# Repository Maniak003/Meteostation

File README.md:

<!DOCTYPE html>
<html lang="en" data-color-mode="auto" data-light-theme="light" data-dark-theme="dark">
  <head>
    <meta charset="utf-8">
  </head>
    <body class="logged-in env-production page-responsive page-blob" style="word-wrap: break-word;">
      <p> Meteostation with radiation monitor. </p>

    </body>
</html>

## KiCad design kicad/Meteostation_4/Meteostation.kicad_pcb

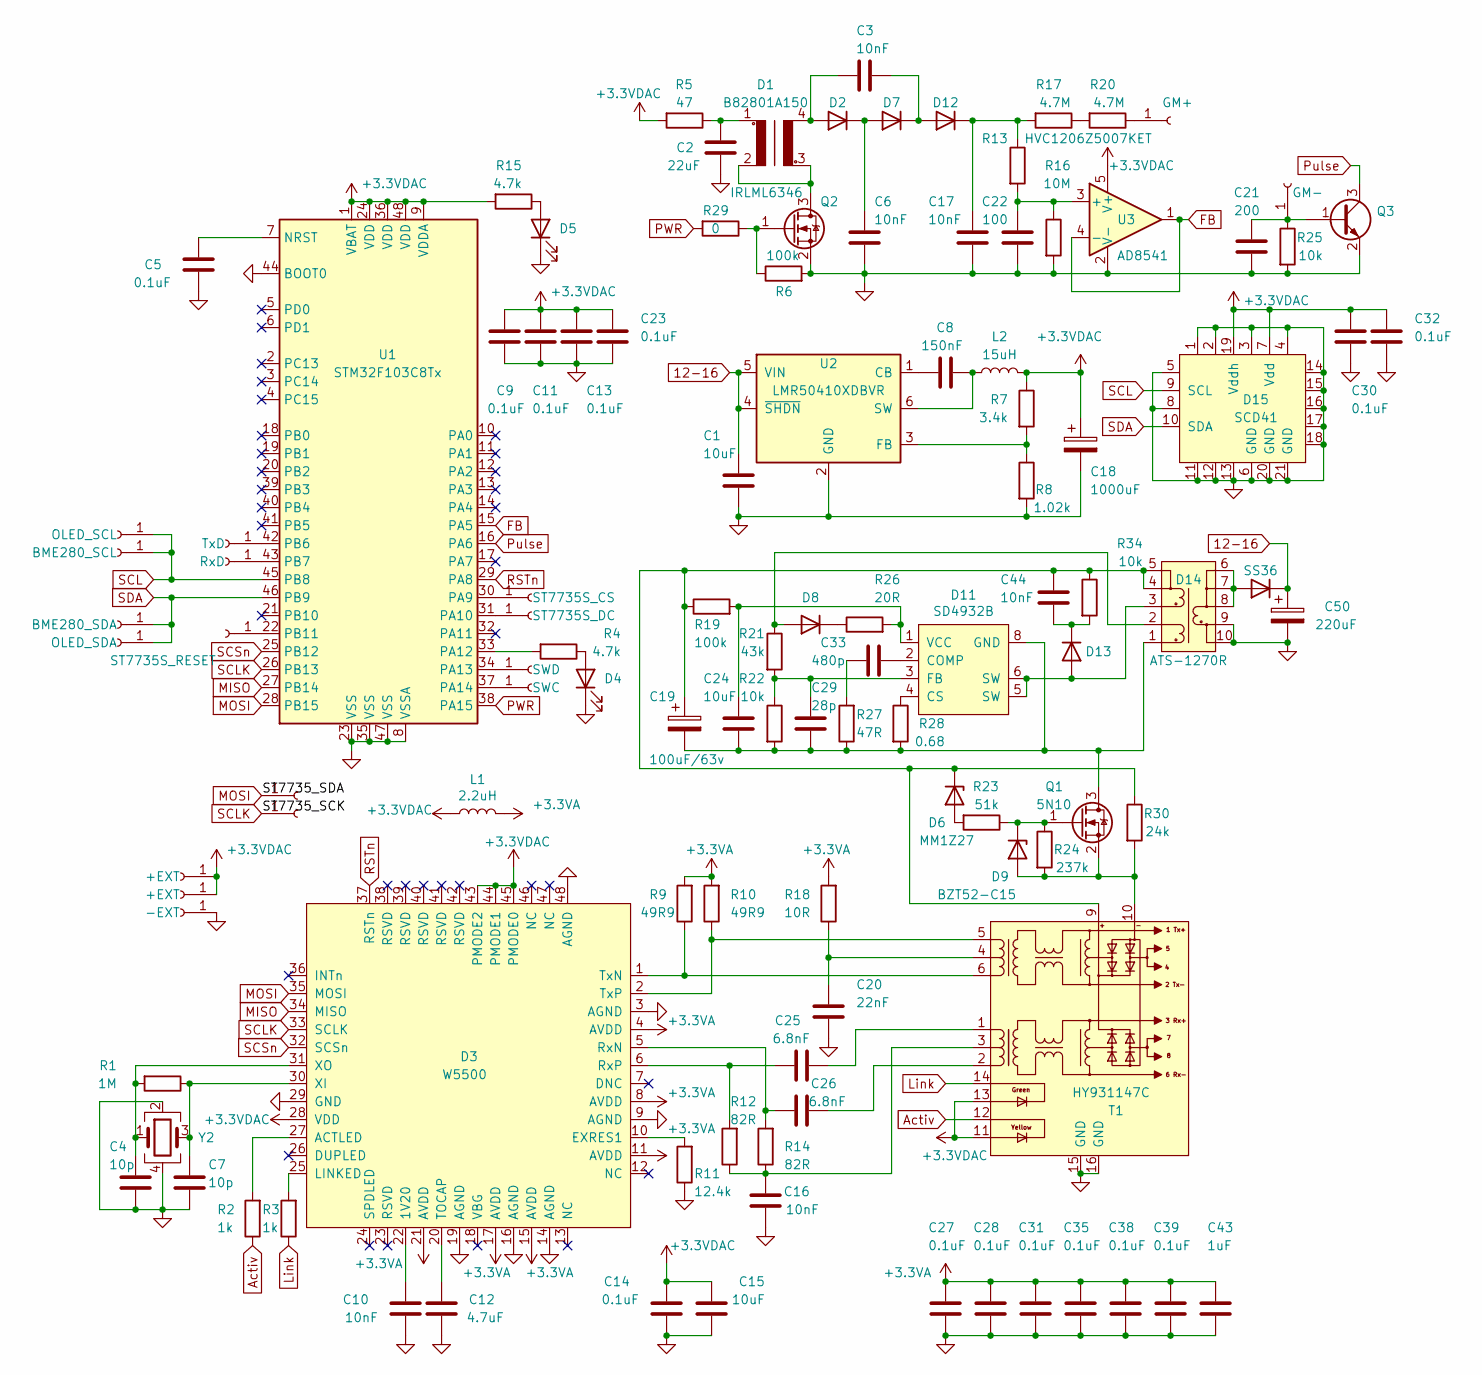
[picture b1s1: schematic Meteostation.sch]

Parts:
C1, C24: 10uF; C_0805_2012Metric
C2: 22uF; C_0805_2012Metric
C3, C6, C17: 10nF; C_1206_3216Metric
C4, C7: 10p; C_0402_1005Metric
C5, C14, C27, C28, C31, C35, C38, C39: 0.1uF; C_0402_1005Metric
C8: 150nF; C_0603_1608Metric
C9, C11, C13, C30, C32: 0.1uF; C_0603_1608Metric
C10: 10nF; C_0402_1005Metric
C12: 4.7uF; C_0402_1005Metric
C15: 10uF; C_0603_1608Metric
C16, C44: 10nF; C_0603_1608Metric
C18: 1000uF; CP_EIA-7343-15_Kemet-W
C19: 100uF/63v; CAP_horizontal
C20: 22nF; C_0603_1608Metric
C21: 200; C_0402_1005Metric
C22: 100; C_0402_1005Metric
C23: 0.1uF; C_0805_2012Metric
C25, C26: 6.8nF; C_0402_1005Metric
C29: 28p; C_0603_1608Metric
C33: 480p; C_0603_1608Metric
C43: 1uF; C_0402_1005Metric
C50: 220uF; CP_EIA-7343-15_Kemet-W
D1: B82801A150; B82801A1
D2, D7, D12: D; D_SOD-123
D3: W5500; LQFP-48_7x7mm_P0.5mm
D4, D5: LED; LED_0603_1608Metric
D6: MM1Z27; D_SOD-123
D8, D13: FR107W F7; D_SOD-123F
D9: BZT52-C15; D_SOD-123
D11: SD4932B; SOIC-8-N7_3.9x4.9mm_P1.27mm
D14: ATS-1270R; DA2257
D15: SCD41
D16: SS36; D_SMA
J1: TxD; ConnMini
J2: RxD; ConnMini
J3: BME280_SCL; SMD-CONN
J4: BME280_SDA; SMD-CONN
J5: +EXT; ConnMini
J6: +EXT; SMD-CONN
J7: -EXT; SMD-CONN
J8: mosi; ConnMini
J9: sclk; ConnMini
J10: GM+; SMD-CONN
J11: GM-; SMD-CONN
J12: SWD; ConnMini
J13: SWC; ConnMini
J14: ST7735S_CS; mini_conn
J15: OLED_SCL; SMD-CONN
J16: OLED_SDA; SMD-CONN
J17: ST7735S_DC; mini_conn
J18: ST7735S_RESET; mini_conn
L1: 2.2uH; L_0805_2012Metric
L2: 15uH; L_Abracon_ASPI-0630LR
Q1: 5N10; SOT-23
Q2: IRLML6346; SOT-23
Q3: Q_NPN_BEC; SOT-23
R1: 1M; R_0402_1005Metric
R2, R3: 1k; R_0402_1005Metric
R4: 4.7k; R_0402_1005Metric
R5: 47; R_1206_3216Metric
R6, R19: 100k; R_0603_1608Metric
R7: 3.4k; R_0603_1608Metric
R8: 1.02k; R_0603_1608Metric
R9, R10: 49R9; R_0603_1608Metric
R11: 12.4k; R_0402_1005Metric
R12, R14: 82R; R_0402_1005Metric
R13: HVC1206Z5007KET; R_1206_3216Metric
R15: 4.7k; R_0603_1608Metric
R16: 10M; R_0402_1005Metric
R17, R20: 4.7M; R_0603_1608Metric
R18: 10R; R_0603_1608Metric
R21: 43k; R_0603_1608Metric
R22, R34: 10k; R_0603_1608Metric
R23: 51k; R_0603_1608Metric
R24: 237k; R_0603_1608Metric
R25: 10k; R_0402_1005Metric
R26: 20R; R_0603_1608Metric
R27: 47R; R_0603_1608Metric
R28: 0.68; R_0603_1608Metric
R29: 0; R_1206_3216Metric
R30: 24k; R_0603_1608Metric
T1: HY931147C
U1: STM32F103C8Tx; LQFP-48_7x7mm_P0.5mm
U2: LMR50410XDBVR; SOT-23-6
U3: AD8541; TSOT-23-5
Y2: ECS-250-20-33 25MHz; Crystal_SMD_SeikoEpson_FA238-4Pin_3.2x2.5mm

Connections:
12-16: C1.1, C50.1, D16.1 (K), U2.4 (~SHDN), U2.5 (VIN)
+3.3VA: C27.1, C28.1, C31.1, C35.1, C38.1, C39.1, C43.1, D3.4 (AVDD), D3.8 (AVDD), D3.11 (AVDD), D3.15 (AVDD), D3.17 (AVDD), D3.21 (AVDD), L1.2, R9.2, R10.2, R18.2
+3.3VDAC: C9.1, C11.1, C13.1, C14.2, C15.2, C18.1, C23.1, C30.1, C32.1, D3.28 (VDD), D3.43 (PMODE2), D3.44 (PMODE1), D3.45 (PMODE0), D15.7 (Vdd), D15.19 (Vddh), J5.1, J6.1, L1.1, L2.2, R5.2, R7.1, R15.2, T1.11, T1.13, U1.1 (VBAT), U1.9 (VDDA), U1.24 (VDD), U1.36 (VDD), U1.48 (VDD), U3.5 (V+)
Activ: R2.1, T1.12
FB: U1.15 (PA5), U3.1, U3.4 (-)
GND: C1.2, C2.2, C4.2, C5.1, C6.2, C7.2, C9.2, C10.1, C11.2, C12.1, C13.2, C14.1, C15.1, C16.1, C17.2, C18.2, C20.2, C21.1, C22.1, C23.2, C27.2, C28.2, C30.2, C31.2, C32.2, C35.2, C38.2, C39.2, C43.2, C50.2, D3.3 (AGND), D3.9 (AGND), D3.14 (AGND), D3.16 (AGND), D3.19 (AGND), D3.29 (GND), D3.48 (AGND), D4.1 (K), D5.1 (K), D14.9, D14.10, D15.1, D15.2, D15.3, D15.4, D15.5, D15.6 (GND), D15.8, D15.11, D15.12, D15.13, D15.14, D15.15, D15.16, D15.17, D15.18, D15.20 (GND), D15.21 (GND), J7.1, Q2.2 (S), Q3.2 (E), R6.2, R8.2, R11.1, R16.2, R25.2, T1.15 (GND), T1.16 (GND), U1.8 (VSSA), U1.23 (VSS), U1.35 (VSS), U1.44 (BOOT0), U1.47 (VSS), U2.2 (GND), U3.2 (V-), Y2.2, Y2.4
Link: R3.1, T1.14
MISO: D3.34 (MISO), U1.27 (PB14)
MOSI: D3.35 (MOSI), J8.1, U1.28 (PB15)
unnamed: C2.1, D1.1, R5.1
unnamed: C16.2, R12.1, R14.1, T1.3
unnamed: C20.1, R18.1, T1.4
unnamed: C25.2, T1.1
unnamed: C26.2, T1.2
unnamed: C33.2, R27.2
unnamed: C3.2, D1.4, D2.2 (A)
unnamed: C6.1, D2.1 (K), D7.2 (A)
unnamed: C10.2, D3.22 (1V20)
unnamed: D3.27 (ACTLED), R2.2
unnamed: D3.10 (EXRES1), R11.2
unnamed: D3.25 (LINKED), R3.2
unnamed: C26.1, D3.5 (RxN), R14.2
unnamed: C25.1, D3.6 (RxP), R12.2
unnamed: C12.2, D3.20 (TOCAP)
unnamed: D3.1 (TxN), R9.1, T1.6
unnamed: D3.2 (TxP), R10.1, T1.5
unnamed: C7.1, D3.30 (XI), R1.1, Y2.3
unnamed: C4.1, D3.31 (XO), R1.2, Y2.1
unnamed: D4.2 (A), R4.1
unnamed: D5.2 (A), R15.1
unnamed: D6.2 (A), R23.2
unnamed: C19.1, C44.1, D6.1 (K), D14.4, D14.5, R19.1, R30.1, R34.1, T1.9
unnamed: D8.2 (A), D14.2, R21.1
unnamed: D8.1 (K), R26.1
unnamed: D9.2 (A), Q1.2 (S), R24.2, R30.2, T1.10
unnamed: D9.1 (K), Q1.1 (G), R23.1, R24.1
unnamed: C33.1, D11.2 (COMP)
unnamed: D11.4 (CS), R28.1
unnamed: C29.1, D11.3 (FB), R21.2, R22.1
unnamed: C19.2, C24.2, C29.2, D11.8 (GND), D14.1, Q1.3 (D), R22.2, R27.1, R28.2
unnamed: C24.1, D11.1 (VCC), R19.2, R26.2
unnamed: C3.1, D7.1 (K), D12.2 (A)
unnamed: C17.1, D12.1 (K), R13.1, R17.2
unnamed: D11.5 (SW), D11.6 (SW), D13.2 (A), D14.3
unnamed: C44.2, D13.1 (K), R34.2
unnamed: D14.6, D14.7, D14.8, D16.2 (A)
unnamed: J1.1, U1.42 (PB6)
unnamed: J2.1, U1.43 (PB7)
unnamed: J10.1, R20.1
unnamed: C21.2, J11.1, Q3.1 (B), R25.1
unnamed: J12.1, U1.34 (PA13)
unnamed: J13.1, U1.37 (PA14)
unnamed: J14.1, U1.30 (PA9)
unnamed: J17.1, U1.31 (PA10)
unnamed: J18.1, U1.22 (PB11)
unnamed: D1.2, D1.3, Q2.3 (D)
unnamed: Q2.1 (G), R6.1, R29.1
unnamed: R17.1, R20.2
unnamed: C5.2, U1.7 (NRST)
unnamed: R4.2, U1.33 (PA12)
unnamed: C8.1, U2.1 (CB)
unnamed: R7.2, R8.1, U2.3 (FB)
unnamed: C8.2, L2.1, U2.6 (SW)
unnamed: C22.2, R13.2, R16.1, U3.3 (+)
PWR: R29.2, U1.38 (PA15)
Pulse: Q3.3 (C), U1.16 (PA6)
RSTn: D3.37 (RSTn), U1.29 (PA8)
SCL: D15.9 (SCL), J3.1, J15.1, U1.45 (PB8)
SCLK: D3.33 (SCLK), J9.1, U1.26 (PB13)
SCSn: D3.32 (SCSn), U1.25 (PB12)
SDA: D15.10 (SDA), J4.1, J16.1, U1.46 (PB9)

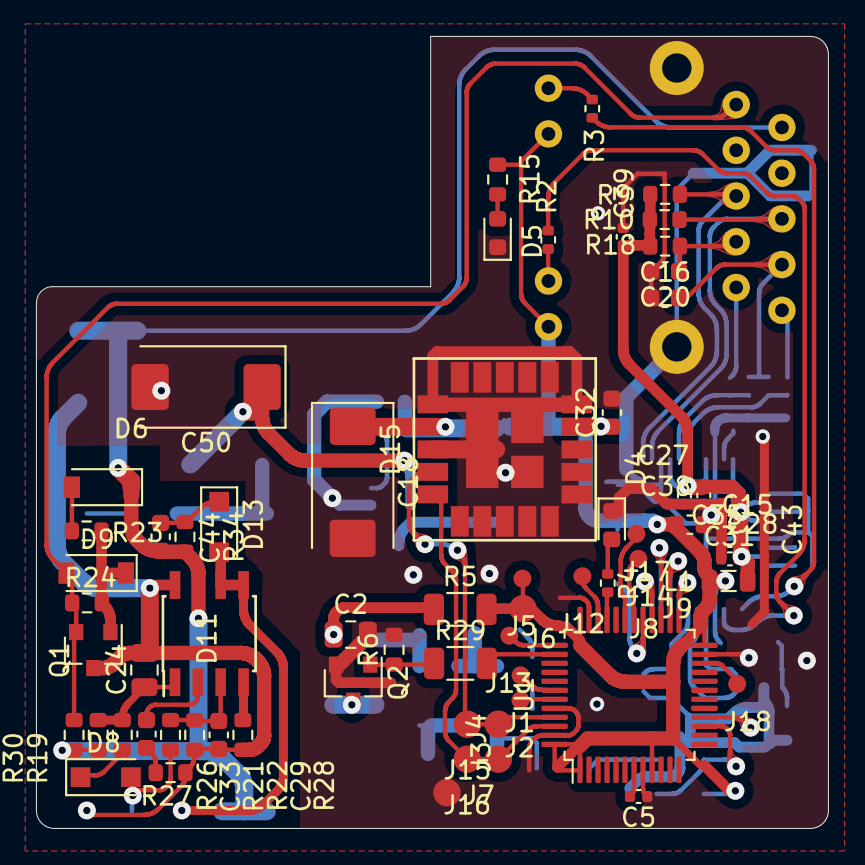
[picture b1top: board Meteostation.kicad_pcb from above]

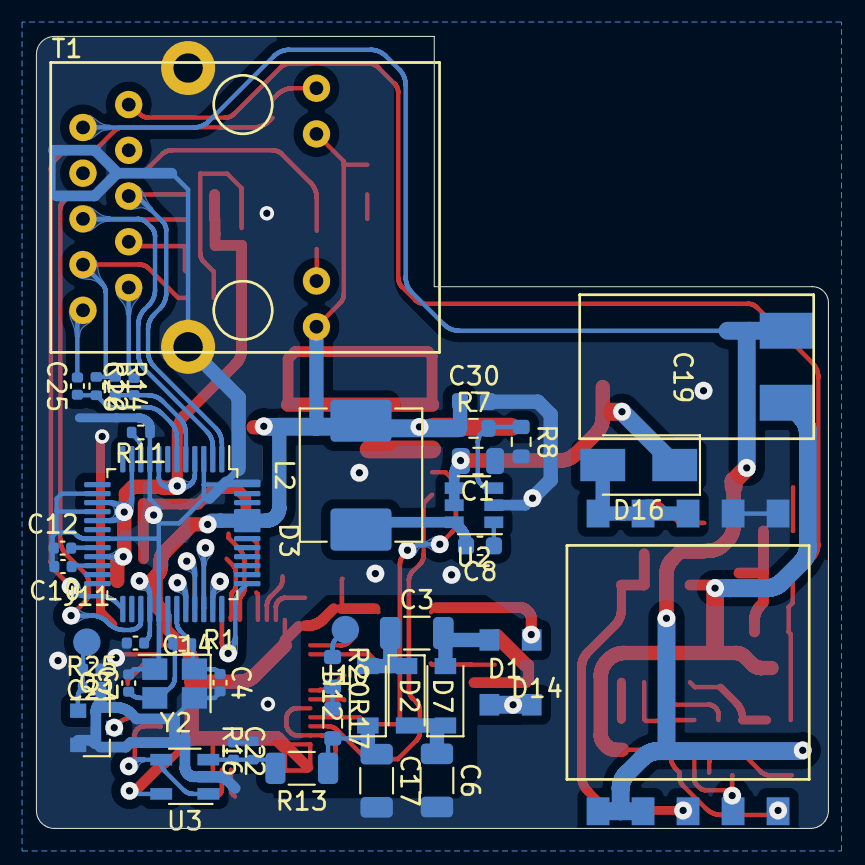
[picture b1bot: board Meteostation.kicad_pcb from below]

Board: 2 copper layers, 44.0 x 44.0 mm, 109 parts (42 on the bottom side), 71 nets.

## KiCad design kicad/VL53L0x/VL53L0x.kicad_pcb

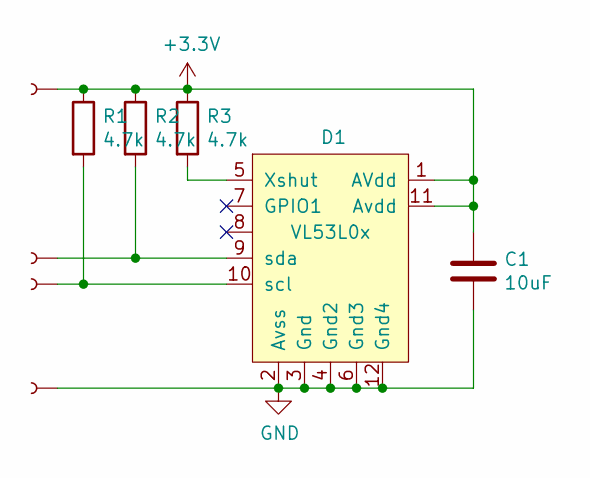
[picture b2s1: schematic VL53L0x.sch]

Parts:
C1: 10uF; C_0402_1005Metric
D1: VL53L0x
J1, J2, J3, J4: Conn; ConnMini
R1, R2, R3: 4.7k; R_0402_1005Metric

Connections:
+3V3: C1.1, D1.1 (AVdd), D1.11 (Avdd), J1.1, R1.1, R2.1, R3.1
GND: C1.2, D1.2 (Avss), D1.3 (Gnd), D1.4 (Gnd2), D1.6 (Gnd3), D1.12 (Gnd4), J4.1
unnamed: D1.5 (Xshut), R3.2
unnamed: D1.9 (sda), J2.1, R2.2
unnamed: D1.10 (scl), J3.1, R1.2

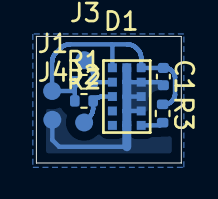
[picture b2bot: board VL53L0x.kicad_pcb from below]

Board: 2 copper layers, 8.1 x 7.0 mm, 9 parts (9 on the bottom side), 5 nets.

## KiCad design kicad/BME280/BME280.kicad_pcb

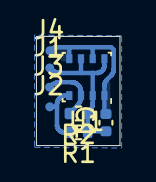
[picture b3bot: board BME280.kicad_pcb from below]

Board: 2 copper layers, 4.6 x 6.1 mm, 8 parts (8 on the bottom side), 4 nets.

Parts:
C1: 0.1uF; C_0402_1005Metric
J1, J2, J3, J4: Conn; ConnMini
R1, R2: 5.1k; R_0402_1005Metric
U1: BME280; Bosch_LGA-8_2.5x2.5mm_P0.65mm_ClockwisePinNumbering

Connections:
Gnd: C1.2, J4.1, U1.1, U1.5, U1.7
SCL: J2.1, R1.2, U1.4
SDA: J3.1, R2.2, U1.3
Vcc: C1.1, J1.1, R1.1, R2.1, U1.2, U1.6, U1.8

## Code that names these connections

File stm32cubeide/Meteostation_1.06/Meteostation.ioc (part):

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Mcu.UserName=STM32F103C8Tx
PA12.GPIOParameters=GPIO_Speed,PinState,GPIO_Label
PA9.GPIOParameters=GPIO_Label
PA6.GPIO_Label=PULSE_GM
PB11.Signal=GPIO_Output
PB15.Signal=SPI2_MOSI
PB13.Signal=SPI2_SCK
RCC.SYSCLKSource=RCC_SYSCLKSOURCE_PLLCLK
PA15.GPIO_Label=POWER_PULSE
PA12.Signal=GPIO_Output
PB6.Signal=USART1_TX
PB6.Mode=Asynchronous
PA8.GPIOParameters=GPIO_Label
PA12.PinState=GPIO_PIN_RESET
PB12.GPIO_Label=Eth_CS
PA6.GPIO_PuPd=GPIO_PULLUP
PB14.Mode=Full_Duplex_Master
PA10.GPIO_Label=ST7735S_DC
PB7.Signal=USART1_RX
PA8.Signal=GPIO_Output
PB9.Signal=I2C1_SDA
Mcu.Package=LQFP48
PA6.Signal=GPXTI6
PA10.Signal=GPIO_Output
PA15.Signal=GPIO_Output
PA5.GPIOParameters=GPIO_Label
PB13.Mode=Full_Duplex_Master
PA12.GPIO_Speed=GPIO_SPEED_FREQ_HIGH
PA6.GPIOParameters=GPIO_PuPd,GPIO_Label,GPIO_ModeDefaultEXTI
PA6.GPIO_ModeDefaultEXTI=GPIO_MODE_IT_RISING
PB8.GPIOParameters=GPIO_Label
PB9.GPIO_Label=BME280_SDA
PA15.GPIOParameters=GPIO_Speed,GPIO_Label
PA9.GPIO_Label=ST7735S_CS
PB11.GPIO_Label=ST7735S_RESET
PA12.GPIO_Label=LED
PB9.GPIOParameters=GPIO_Label
PB8.GPIO_Label=BME280_SCL
PA8.GPIO_Label=Eth_rst
PB9.Mode=I2C
PA9.Signal=GPIO_Output
PB11.GPIOParameters=GPIO_Label
PB12.GPIO_Speed=GPIO_SPEED_FREQ_HIGH
PB14.Signal=SPI2_MISO
PA5.Signal=ADCx_IN5
board=custom
PB15.Mode=Full_Duplex_Master
PA10.GPIOParameters=GPIO_Label
Mcu.Name=STM32F103C(8-B)Tx
RCC.SYSCLKFreq_VALUE=64000000
PA5.GPIO_Label=FB
RCC.HSEDivPLL=RCC_HSE_PREDIV_DIV2
PA15.GPIO_Speed=GPIO_SPEED_FREQ_HIGH
PB7.Mode=Asynchronous
PB8.Mode=I2C
PB8.Signal=I2C1_SCL
PB12.GPIOParameters=GPIO_Speed,GPIO_Label
PB12.Signal=GPIO_Output

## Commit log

2022-09-04 удалено: Documents/12_100229_1_85526.pdf удалено: Documents/2022_04_03_20_00_22_110.png удалено: Documents/Diagram.pdf удалено: Documents/IMG_20220105_221915.jpg удалено: Documents/IMG_20220105_22192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
2022-09-04 новый файл: Arduino/meteomonitor/meteomonitor.ino новый файл: FreeCAD/box.FCStd новый файл: FreeCAD/box.stl
2022-09-05 изменено: kicad/Meteostation_3/Meteostation.kicad_pcb изменено: kicad/Meteostation_3/Meteostation.kicad_pcb-bak изменено: kicad/Meteostation_3/Meteostation.sch изменено: kicad/Meteostation_3/Meteosta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
2022-09-05 изменено: FreeCAD/box.FCStd изменено: FreeCAD/box.stl
2022-09-08 изменено: FreeCAD/box.FCStd изменено: FreeCAD/box.stl новый файл: kicad/Meteostation_4/Meteostation-cache.lib новый файл: kicad/Meteostation_4/Meteostation-rescue.bck новый файл: kicad/Meteostation_4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
2022-09-08 новый файл: Documents/Sensirion_CO2_Sensors_SCD4x_Datasheet.pdf
2022-09-09 новый файл: Documents/5N10.pdf изменено: kicad/Meteostation_4/Meteostation.kicad_pcb изменено: kicad/Meteostation_4/Meteostation.kicad_pcb-bak изменено: kicad/Meteostation_4/Meteostation.sch изменено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
2022-09-11 изменено: kicad/Meteostation_4/Meteostation-cache.lib изменено: kicad/Meteostation_4/Meteostation-rescue.lib изменено: kicad/Meteostation_4/Meteostation.kicad_pcb изменено: kicad/Meteostation_4/Meteo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
2022-09-13 изменено: kicad/Meteostation_4/gerber/Meteostation.zip новый файл: stm32cubeide/Meteostation/.cproject новый файл: stm32cubeide/Meteostation/.mxproject новый файл: stm32cubeide/Meteostation/.project 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
2022-09-13 новый файл: Documents/AN_SE_0119_0177_AN168_Revised8.pdf новый файл: Documents/AN_SE_0119_Connecting_Arduino_Revised8.pdf новый файл: Documents/DS_SE_0119_CM_0177_Revised8.pdf новый файл: Documents/M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
2022-09-13 изменено: kicad/Meteostation_4/Meteostation.kicad_pcb
2022-09-15 изменено: kicad/Meteostation_4/Meteostation.kicad_pcb изменено: kicad/Meteostation_4/Meteostation.kicad_pcb-bak изменено: kicad/Meteostation_4/Meteostation.sch изменено: kicad/Meteostation_4/Meteosta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
2022-09-17 изменено: kicad/Meteostation_4/Meteostation.sch изменено: kicad/Meteostation_4/Meteostation.sch-bak
2022-09-18 изменено: stm32cubeide/Meteostation/.cproject изменено: stm32cubeide/Meteostation/.mxproject изменено: stm32cubeide/Meteostation/Core/Inc/main.h изменено: stm32cubeide/Meteostation/Core/Inc/stm32f1xx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
2022-09-19 изменено: kicad/Meteostation_4/Meteostation.kicad_pcb изменено: kicad/Meteostation_4/Meteostation.kicad_pcb-bak изменено: kicad/Meteostation_4/Meteostation.sch изменено: kicad/Meteostation_4/Meteosta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
2022-09-19 изменено: kicad/Meteostation_4/Meteostation.sch изменено: kicad/Meteostation_4/Meteostation.sch-bak изменено: stm32cubeide/Meteostation/.mxproject изменено: stm32cubeide/Meteostation/Core/Inc/main.h 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
2022-09-21 изменено: kicad/Meteostation_4/Meteostation.kicad_pcb изменено: kicad/Meteostation_4/Meteostation.kicad_pcb-bak изменено: kicad/Meteostation_4/Meteostation.sch изменено: kicad/Meteostation_4/Meteosta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
2022-09-21 изменено: stm32cubeide/Meteostation/Meteostation.ioc изменено: stm32cubeide/Meteostation/Release/Core/Src/main.o изменено: stm32cubeide/Meteostation/Release/Meteostation.bin изменено: stm32cubeide/Me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
2022-09-21 новый файл: stm32cubeide/Meteostation/Core/Src/BME280.c новый файл: stm32cubeide/Meteostation/Core/Src/dhcp.c новый файл: stm32cubeide/Meteostation/Core/Src/main.c новый файл: stm32cubeide/Meteostati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
2022-09-21 новый файл: stm32cubeide/Meteostation/Core/Inc/ssd1306.h новый файл: stm32cubeide/Meteostation/Core/Inc/ssd1306_conf.h новый файл: stm32cubeide/Meteostation/Core/Inc/ssd1306_conf_template.h новый фай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
2022-09-21 изменено: stm32cubeide/Meteostation/.cproject изменено: stm32cubeide/Meteostation/.mxproject изменено: stm32cubeide/Meteostation/Core/Inc/main.h изменено: stm32cubeide/Meteostation/Core/Src/main.c из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
2022-09-21 новый файл: stm32cubeide/Meteostation/Core/Inc/sntp.h новый файл: stm32cubeide/Meteostation/Core/Src/sntp.c
2022-09-21 изменено: stm32cubeide/Meteostation/Core/Inc/dhcp.h изменено: stm32cubeide/Meteostation/Core/Inc/main.h изменено: stm32cubeide/Meteostation/Core/Inc/wizchip_conf.h изменено: stm32cubeide/Meteostation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
2022-09-22 изменено: stm32cubeide/Meteostation/.mxproject изменено: stm32cubeide/Meteostation/Core/Inc/main.h изменено: stm32cubeide/Meteostation/Core/Inc/stm32f1xx_it.h изменено: stm32cubeide/Meteostation/Core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
2022-09-27 новый файл: FreeCAD/GM_case.FCStd новый файл: FreeCAD/GM_case_top.FCStd новый файл: FreeCAD/box2.FCStd
2022-09-27 изменено: stm32cubeide/Meteostation/Core/Src/main.c Documents/lmr14206.pdf stm32cubeide/Meteostation/.settings/language.settings.xml stm32cubeide/Meteostation/Drivers/STM32F1xx_HAL_Driver/Inc/stm32f1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
2022-09-27 изменено: stm32cubeide/Meteostation/Core/Src/ssd1306.c изменено: stm32cubeide/Meteostation/Release/Meteostation.bin изменено: stm32cubeide/Meteostation/Release/Meteostation.elf изменено: stm32cubeide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
2022-09-27 новый файл: Documents/lmr14206.pdf новый файл: stm32cubeide/Meteostation/.settings/language.settings.xml новый файл: stm32cubeide/Meteostation/Meteostation.launch
2022-09-28 новый файл: kicad/BME280/BME280-cache.lib новый файл: kicad/BME280/BME280.kicad_pcb новый файл: kicad/BME280/BME280.kicad_pcb-bak новый файл: kicad/BME280/BME280.pro новый файл: kicad/BME280/BME280.s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
2022-09-28 изменено: FreeCAD/box2.FCStd новый файл: FreeCAD/cover.FCStd
2022-09-29 изменено: FreeCAD/cover.FCStd FreeCAD/GM_case.stl FreeCAD/GM_case_top.stl FreeCAD/box2.stl FreeCAD/cover.stl
2022-10-01 изменено: kicad/BME280/fp-info-cache изменено: kicad/Meteostation_3/Meteostation.sch изменено: kicad/Meteostation_3/Meteostation.sch-bak
2022-10-19 изменено: kicad/Meteostation_4/Meteostation.sch изменено: kicad/Meteostation_4/Meteostation.sch-bak изменено: stm32cubeide/Meteostation/.settings/language.settings.xml
2022-10-20 новый файл: Documents/IMG_20221019_081842.jpg новый файл: Documents/sheet.png изменено: README.md
2022-10-20 изменено: README.md
2022-10-23 изменено: Arduino/meteomonitor/meteomonitor.ino изменено: stm32cubeide/Meteostation/.cproject изменено: stm32cubeide/Meteostation/.settings/language.settings.xml изменено: stm32cubeide/Meteostation/C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
2022-10-23 изменено: stm32cubeide/Meteostation/.settings/language.settings.xml изменено: stm32cubeide/Meteostation/Core/Src/main.c изменено: stm32cubeide/Meteostation/Release/Core/Src/main.o изменено: stm32cube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
2022-10-24 изменено: stm32cubeide/Meteostation/.mxproject изменено: stm32cubeide/Meteostation/.settings/language.settings.xml изменено: stm32cubeide/Meteostation/Core/Inc/main.h изменено: stm32cubeide/Meteostat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
2022-10-24 новый файл: stm32cubeide/Meteostation/Core/Inc/SCD41.h
2022-10-28 изменено: kicad/Meteostation_4/Meteostation.kicad_pcb изменено: kicad/Meteostation_4/Meteostation.kicad_pcb-bak изменено: kicad/Meteostation_4/Meteostation.pro изменено: kicad/Meteostation_4/Meteosta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
2022-11-08 изменено: kicad/Meteostation_4/Meteostation.kicad_pcb изменено: kicad/Meteostation_4/Meteostation.kicad_pcb-bak
2022-11-11 изменено: kicad/Meteostation_4/Meteostation.kicad_pcb изменено: kicad/Meteostation_4/Meteostation.kicad_pcb-bak изменено: kicad/Meteostation_4/Meteostation.sch изменено: kicad/Meteostation_4/Meteosta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
2022-11-17 изменено: kicad/Meteostation_4/Meteostation-rescue.lib изменено: kicad/Meteostation_4/gerber/Border.gbr изменено: kicad/Meteostation_4/gerber/Bottom.gbr изменено: kicad/Meteostation_4/gerber/MaskBott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
2022-11-17 новый файл: Documents/vl53l0x.pdf
2022-11-18 новый файл: stm32cubeide/VL53L0x/en.STSW-IMG005.zip
2022-12-05 изменено: kicad/Meteostation_4/gerber/Border.gbr изменено: kicad/Meteostation_4/gerber/Bottom.gbr изменено: kicad/Meteostation_4/gerber/MaskBottom.gbr изменено: kicad/Meteostation_4/gerber/MaskTop.gb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
2022-12-05 новый файл: Release/all.zip
2023-01-07 изменено: kicad/Meteostation_4/Meteostation.sch изменено: kicad/Meteostation_4/Meteostation.sch-bak изменено: stm32cubeide/Meteostation/.mxproject изменено: stm32cubeide/Meteostation/.settings/langua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
2023-01-08 изменено: stm32cubeide/Meteostation/Core/Inc/main.h изменено: stm32cubeide/Meteostation/Core/Src/main.c изменено: stm32cubeide/Meteostation/Release/Core/Src/BME280.d изменено: stm32cubeide/Meteostati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
2023-01-08 новый файл: FreeCAD/box2.stl
2023-01-09 изменено: Documents/sheet.png изменено: kicad/Meteostation_4/Meteostation-cache.lib изменено: kicad/Meteostation_4/Meteostation.kicad_pcb изменено: kicad/Meteostation_4/Meteostation.kicad_pcb-bak изм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
2023-01-24 новый файл: Documents/IMG_20230122_160000.png изменено: kicad/BME280/BME280.kicad_pcb изменено: kicad/BME280/BME280.kicad_pcb-bak
2023-06-04 изменено: Arduino/meteomonitor/meteomonitor.ino изменено: FreeCAD/GM_case_top.FCStd изменено: kicad/Meteostation_4/Meteostation-cache.lib изменено: kicad/Meteostation_4/Meteostation-rescue.lib измене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
2023-06-05 новый файл: stm32cubeide/Meteostation/Core/Inc/GFX_FUNCTIONS.h новый файл: stm32cubeide/Meteostation/Core/Inc/ST7735_fonts.h новый файл: stm32cubeide/Meteostation/Core/Inc/st7735.h новый файл: stm32c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
2023-06-07 изменено: kicad/Meteostation_4/Meteostation.kicad_pcb изменено: kicad/Meteostation_4/Meteostation.kicad_pcb-bak изменено: kicad/Meteostation_4/Meteostation.sch изменено: kicad/Meteostation_4/Meteosta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
2023-06-07 изменено: kicad/Meteostation_4/fp-info-cache
2023-06-11 новый файл: Documents/IMG_20230604_182714.jpg изменено: README.md
2023-06-12 изменено: stm32cubeide/Meteostation/Core/Src/main.c
2023-07-15 New case
2024-02-05 изменено: FreeCAD/GM_case.FCStd изменено: kicad/BME280/BME280.kicad_pcb изменено: kicad/Meteostation_4/Meteostation-rescue.lib изменено: kicad/Meteostation_4/Meteostation.kicad_pcb изменено: stm32cub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
2024-02-05 новый файл: FreeCAD/box3.FCStd новый файл: FreeCAD/co2holder.FCStd новый файл: FreeCAD/face.FCStd
2024-02-05 изменено: FreeCAD/box3.FCStd изменено: kicad/Meteostation_4/fp-info-cache
2024-12-31 изменено: stm32cubeide/Meteostation/.cproject изменено: stm32cubeide/Meteostation/.mxproject изменено: stm32cubeide/Meteostation/.settings/language.settings.xml изменено: stm32cubeide/Meteostation/.s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
2024-12-31 новый файл: stm32cubeide/Meteostation_1.06/.cproject новый файл: stm32cubeide/Meteostation_1.06/.mxproject новый файл: stm32cubeide/Meteostation_1.06/.project новый файл: stm32cubeide/Meteostation_1.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
2024-12-31 изменено: stm32cubeide/Meteostation_1.06/Core/Inc/main.h изменено: stm32cubeide/Meteostation_1.06/Core/Src/main.c изменено: stm32cubeide/Meteostation_1.06/Release/Core/Src/main.o изменено: stm32cubei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
2024-12-31 изменено: stm32cubeide/Meteostation_1.06/Core/Src/main.c изменено: stm32cubeide/Meteostation_1.06/Release/Core/Src/main.o изменено: stm32cubeide/Meteostation_1.06/Release/Core/Src/main.su изменено: s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
2025-01-11 изменено: stm32cubeide/Meteostation_1.06/Core/Inc/main.h изменено: stm32cubeide/Meteostation_1.06/Release/Core/Src/main.o изменено: stm32cubeide/Meteostation_1.06/Release/Meteostation.bin изменено: s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
2025-01-11 изменено: FreeCAD/face.FCStd
